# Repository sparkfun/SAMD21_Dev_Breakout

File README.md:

SparkFun SAMD21 Dev Breakout
========================================

[*SparkFun SAMD21 Dev Breakout (DEV-13672)*](https://www.sparkfun.com/products/13672)

The SAMD21 Dev Breakout is an Arduino-sized breakout for the Atmel [ATSAMD21G18](http://www.atmel.com/devices/ATSAMD21G18A.aspx), a 32-bit ARM Cortex-M0+ processor with 256KB flash, 32KB SRAM, and an operating speed of up to 48MHz. The SAMD21 is compatible with the Arduino IDE, and libraries for the Arduino Zero.

Repository Contents
-------------------

* **/Documentation** - Data sheets, additional product information
* **/Firmware** - SAM_BA SAMD21 Bootloader
* **/Hardware** - Eagle design files (.brd, .sch)
* **/Production** - Production panel files (.brd)

Documentation
--------------
* **[Hookup Guide](https://learn.sparkfun.com/tutorials/samd21-Devdev-breakout-hookup-guide/resources--going-further)** - Basic hookup guide for the SAMD21 Dev Breakout.

Product Versions
----------------
* [DEV-13672](https://www.sparkfun.com/products/13672) - Initial product release - v10.
* [DEV-13672](https://www.sparkfun.com/products/13664) - The SparkFun SAMD21 _Mini_ Breakout -- a similar, Arduino-shaped version of this board.

Version History
---------------
* [v1.0](https://github.com/sparkfun/SAMD21_Dev_Breakout/tree/v10) - Initial release 

License Information
-------------------

This product is _**open source**_! 

Please review the LICENSE.md file for license information. 

If you have any questions or concerns on licensing, please contact techsupport@sparkfun.com.

Distributed as-is; no warranty is given.

- Your friends at SparkFun.

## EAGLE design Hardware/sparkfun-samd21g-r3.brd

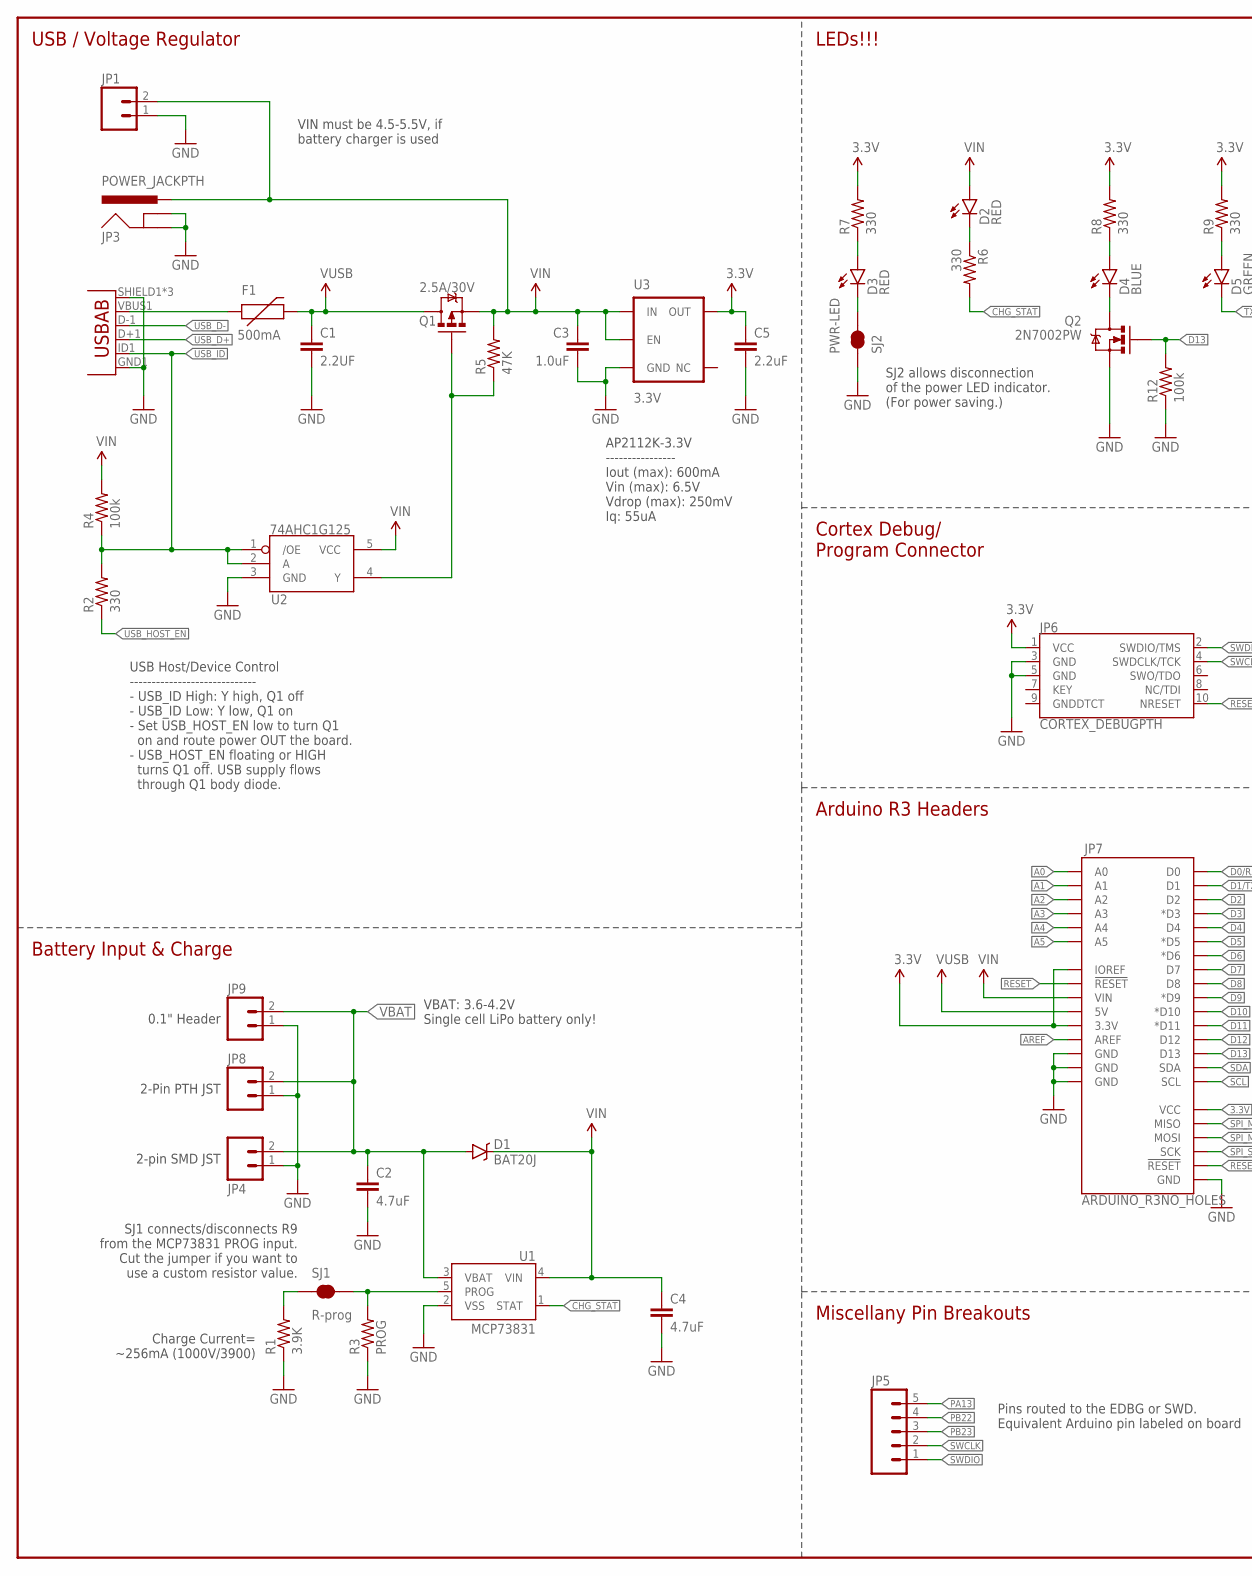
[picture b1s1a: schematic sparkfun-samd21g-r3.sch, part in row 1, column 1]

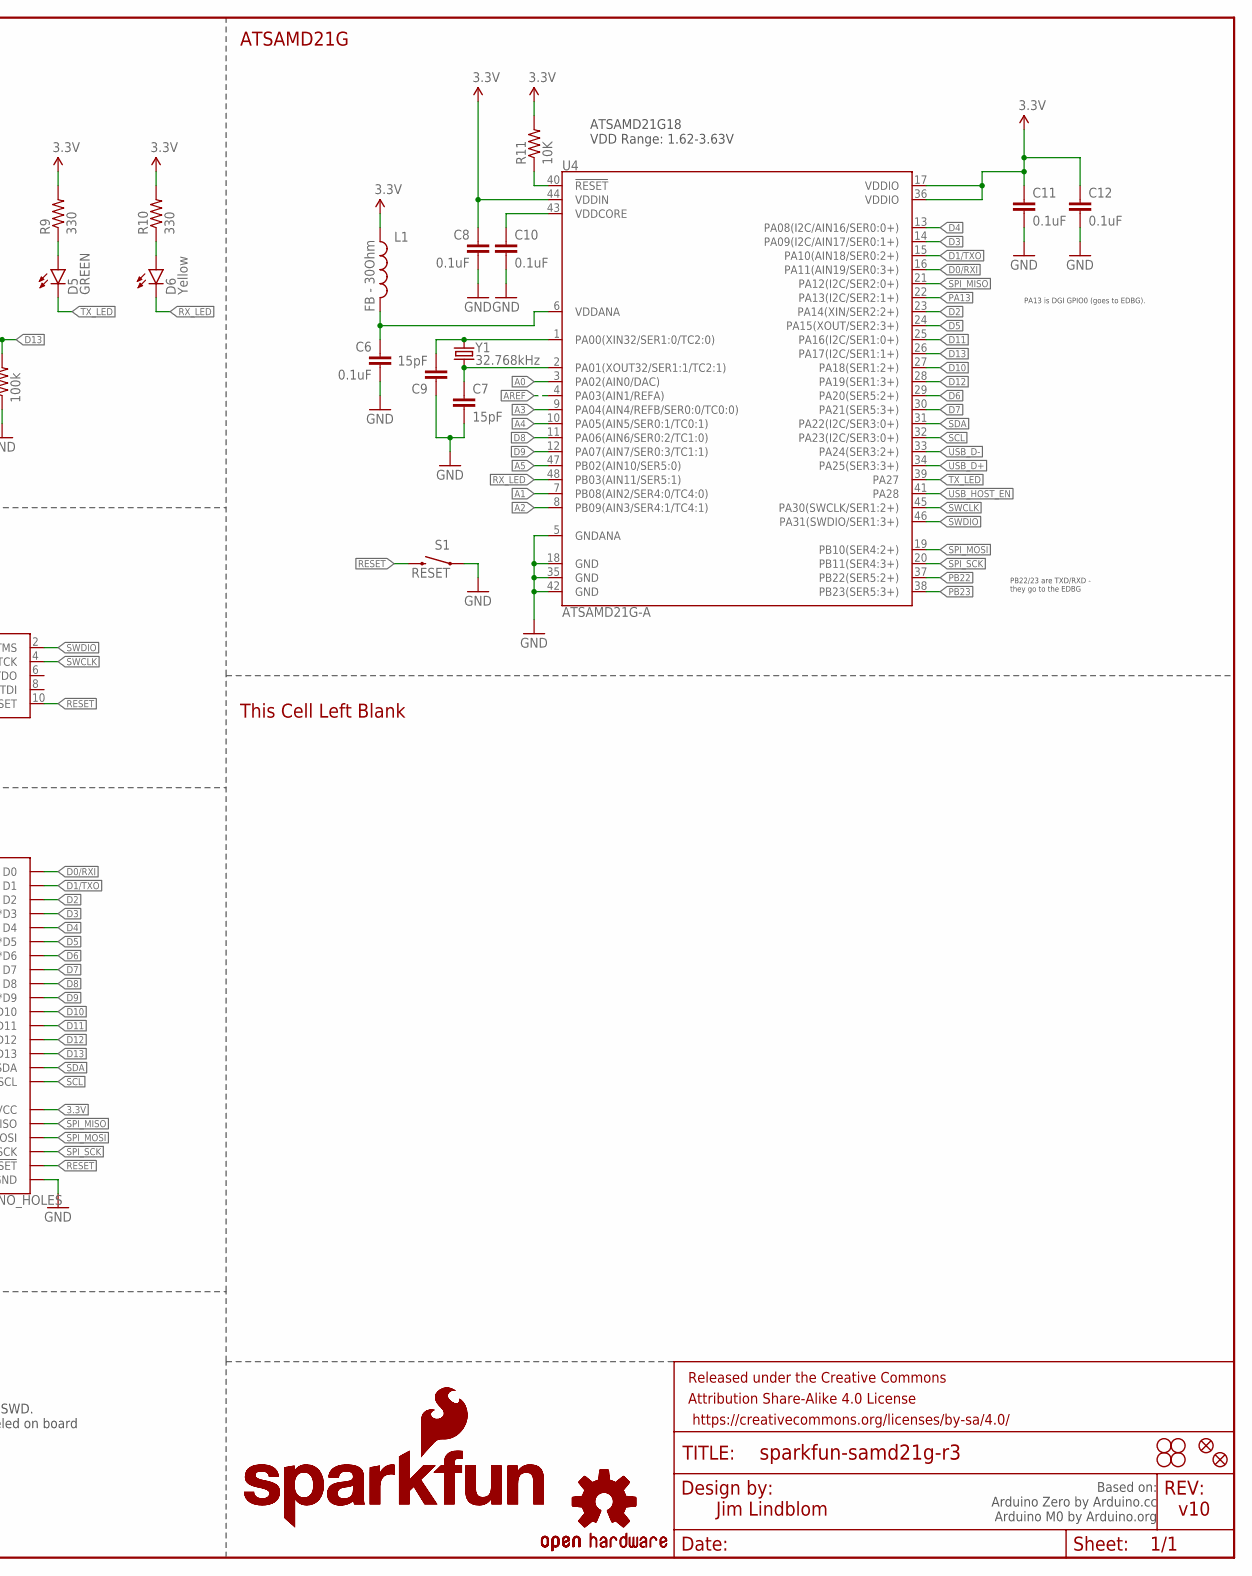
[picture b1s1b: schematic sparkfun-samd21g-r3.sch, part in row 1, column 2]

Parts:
C1: 2.2UF; 1206
C2, C4: 4.7uF; 0603-CAP
C3: 1.0uF; 0805-CAP
C5: 2.2uF; 0603-CAP
C6, C8, C10, C11, C12: 0.1uF; 0603-CAP
C7, C9: 15pF; 0603-CAP
D1: BAT20J; SOD-323
D2, D3: RED; LED-0603
D4: BLUE; LED-0603
D5: GREEN; LED-0603
D6: Yellow; LED-0603
F1: 500mA; PTC-1206
FID1, FID2: FIDUCIAL1X2; FIDUCIAL-1X2
FRAME1: FRAME-LEDGER; CREATIVE_COMMONS
JP1: M02PTH; 1X02
JP2: USB-ABCONN-11794; USB-AB-MICRO-SMD_V03
JP3: POWER_JACKPTH; POWER_JACK_PTH
JP4: M02-JST-2MM-SMT; JST-2-SMD
JP5: M05NO_SILK; 1X05_NO_SILK
JP6: CORTEX_DEBUGPTH; 2X5-PTH-1.27MM
JP7: ARDUINO_R3NO_HOLES; ARDUINO_R3_NO_HOLES
JP8: M02-JST-2-PTH-NO_SILK; JST-2-PTH-NS
JP9: M021X02_NO_SILK; 1X02_NO_SILK
L1: FB - 30Ohm; 0603
LOGO1: SFE_LOGO_NAME_FLAME.2_INCH; SFE_LOGO_NAME_FLAME_.2
LOGO2: SFE_LOGO_NAME_FLAME.4_INCH; SFE_LOGO_NAME_FLAME_.4
LOGO3: OSHW-LOGOS; OSHW-LOGO-S
LOGO4: OSHW-LOGOL; OSHW-LOGO-L
Q1: 2.5A/30V; SOT23-3
Q2: 2N7002PW; SOT323
R1: 3.9K; 0603
R2, R6, R7, R8, R9, R10: 330; 0603-RES
R3: PROG; 1/6W-RES
R4, R12: 100k; 0603-RES
R5: 47K; 0603-RES
R11: 10K; 0603-RES
S1: RESET; TACTILE-SWITCH-SMD
SJ1: R-prog; PAD-JUMPER-2-NC_BY_TRACE_YES_SILK
SJ2: PWR-LED; PAD-JUMPER-2-NC_BY_TRACE_NO_SILK
STANDOFF1, STANDOFF2, STANDOFF3, STANDOFF4: STAND-OFF
U1: MCP73831; SOT23-5
U2: 74AHC1G125; SOT23-5
U3: 3.3V; SOT23-5
U4: ATSAMD21G-A; TQFP-48
Y1: 32.768kHz; CRYSTAL-SMD-3.2X1.5MM

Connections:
3.3V: C5.1, C8.1, C11.1, C12.1, JP6.1 (VCC), JP7.3.3V, JP7.IOREF, JP7.VCC, L1.1, R7.2, R8.2, R9.2, R10.2, R11.2, U3.5 (OUT), U4.17 (VDDIO), U4.36 (VDDIO), U4.44 (VDDIN)
!RESET: JP6.10 (NRESET), JP7.RESET@1 (!RESET!), JP7.RESET@2 (!RESET!), R11.1, S1.3 (2), U4.40 (!RESET!)
A0: JP7.A0, U4.3 (PA02(AIN0/DAC))
A1: JP7.A1, U4.7 (PB08(AIN2/SER4:0/TC4:0))
A2: JP7.A2, U4.8 (PB09(AIN3/SER4:1/TC4:1))
A3: JP7.A3, U4.9 (PA04(AIN4/REFB/SER0:0/TC0:0))
A4: JP7.A4, U4.10 (PA05(AIN5/SER0:1/TC0:1))
A5: JP7.A5, U4.47 (PB02(AIN10/SER5:0))
AREF: JP7.AREF, U4.4 (PA03(AIN1/REFA))
CHG_STAT: R6.2, U1.1 (STAT)
D0/RXI: JP7.D0, U4.16 (PA11(AIN19/SER0:3+))
D1/TXO: JP7.D1, U4.15 (PA10(AIN18/SER0:2+))
D2: JP7.D2, U4.23 (PA14(XIN/SER2:2+))
D3: JP7.D3 (*D3), U4.14 (PA09(I2C/AIN17/SER0:1+))
D4: JP7.D4, U4.13 (PA08(I2C/AIN16/SER0:0+))
D5: JP7.D5 (*D5), U4.24 (PA15(XOUT/SER2:3+))
D6: JP7.D6 (*D6), U4.29 (PA20(SER5:2+))
D7: JP7.D7, U4.30 (PA21(SER5:3+))
D8: JP7.D8, U4.11 (PA06(AIN6/SER0:2/TC1:0))
D9: JP7.D9 (*D9), U4.12 (PA07(AIN7/SER0:3/TC1:1))
D10: JP7.D10 (*D10), U4.27 (PA18(SER1:2+))
D11: JP7.D11 (*D11), U4.25 (PA16(I2C/SER1:0+))
D12: JP7.D12, U4.28 (PA19(SER1:3+))
D13: JP7.D13, Q2.1 (G), R12.2, U4.26 (PA17(I2C/SER1:1+))
GND: C1.2, C2.2, C3.2, C4.2, C5.2, C6.2, C7.2, C8.2, C9.1, C10.2, C11.2, C12.2, JP1.1, JP2.GND1 (GND), JP2.SHIELD1 (SHIELD), JP2.SHIELD2 (SHIELD), JP2.SHIELD3 (SHIELD), JP3.GND, JP3.GNDBREAK, JP4.1 (2), JP6.3 (GND), JP6.5 (GND), JP7.GND@1 (GND), JP7.GND@2 (GND), JP7.GND@3 (GND), JP7.GND@4 (GND), JP8.1, JP9.1, Q2.2 (S), R1.1, R3.1, R12.1, S1.1, SJ2.1, U1.2 (VSS), U2.3 (GND), U3.2 (GND), U4.5 (GNDANA), U4.18 (GND), U4.35 (GND), U4.42 (GND)
unnamed: F1.1, JP2.VBUS1 (VBUS)
unnamed: C9.2, U4.1 (PA00(XIN32/SER1:0/TC2:0)), Y1.P$2 (2)
unnamed: D4.C, Q2.3 (D)
unnamed: C7.1, U4.2 (PA01(XOUT32/SER1:1/TC2:1)), Y1.P$1 (1)
unnamed: D3.A, R7.1
unnamed: D4.A, R8.1
unnamed: D2.C, R6.1
unnamed: D5.A, R9.1
unnamed: D6.A, R10.1
unnamed: D3.C, SJ2.2
unnamed: R1.2, SJ1.1
unnamed: R3.2, SJ1.2, U1.5 (PROG)
PA13: JP5.5, U4.22 (PA13(I2C/SER2:1+))
PB22: JP5.4, U4.37 (PB22(SER5:2+))
PB23: JP5.3, U4.38 (PB23(SER5:3+))
RX_LED: D6.C, U4.48 (PB03(AIN11/SER5:1))
SCL: JP7.SCL, U4.32 (PA23(I2C/SER3:0+))
SDA: JP7.SDA, U4.31 (PA22(I2C/SER3:0+))
SPI_MISO: JP7.MISO, U4.21 (PA12(I2C/SER2:0+))
SPI_MOSI: JP7.MOSI, U4.19 (PB10(SER4:2+))
SPI_SCK: JP7.SCK, U4.20 (PB11(SER4:3+))
SWCLK: JP5.2, JP6.4 (SWDCLK/TCK), U4.45 (PA30(SWCLK/SER1:2+))
SWDIO: JP5.1, JP6.2 (SWDIO/TMS), U4.46 (PA31(SWDIO/SER1:3+))
TX_LED: D5.C, U4.39 (PA27)
USB_D+: JP2.D+1 (D+), U4.34 (PA25(SER3:3+))
USB_D-: JP2.D-1 (D-), U4.33 (PA24(SER3:2+))
USB_HOST_EN: R2.1, U4.41 (PA28)
USB_HOST_POWER_EN: Q1.1 (G), R5.1, U2.4 (Y)
USB_ID: JP2.ID1 (USBID), R2.2, R4.1, U2.1 (/OE), U2.2 (A)
VBAT: C2.1, D1.A, JP4.2 (1), JP8.2, JP9.2, U1.3 (VBAT)
VDDANA: C6.1, L1.2, U4.6 (VDDANA)
VDDCORE: C10.1, U4.43 (VDDCORE)
VIN: C3.1, C4.1, D1.C, D2.A, JP1.2, JP3.PWR, JP7.VIN, Q1.2 (S), R4.2, R5.2, U1.4 (VIN), U2.5 (VCC), U3.1 (IN), U3.3 (EN)
VUSB: C1.1, F1.2, JP7.5V, Q1.3 (D)

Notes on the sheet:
PB22/23 are TXD/RXD - they go to the EDBG
PA13 is DGI GPIO0 (goes to EDBG).
USB / Voltage Regulator
LEDs!!!
Cortex Debug/ Program Connector
Arduino R3 Headers
ATSAMD21G
Jim Lindblom
v10
Charge Current= ~256mA (1000V/3900)
SJ1 connects/disconnects R9 from the MCP73831 PROG input. Cut the jumper if you want to use a custom resistor value.
Battery Input & Charge
SJ2 allows disconnection of the power LED indicator. (For power saving.)
Miscellany Pin Breakouts
This Cell Left Blank
VIN must be 4.5-5.5V, if battery charger is used
ATSAMD21G18 VDD Range: 1.62-3.63V
Based on: Arduino Zero by Arduino.cc Arduino M0 by Arduino.org
0.1" Header
2-Pin PTH JST
2-pin SMD JST
AP2112K-3.3V ---------------- Iout (max): 600mA Vin (max): 6.5V Vdrop (max): 250mV Iq: 55uA
USB Host/Device Control ----------------------------- - USB_ID High: Y high, Q1 off - USB_ID Low: Y low, Q1 on - Set USB_HOST_EN low to turn Q1 on and route power OUT the board. - USB_HOST_EN floating or HIGH turns Q1 off. USB supply flows through Q1 body diode.
Pins routed to the EDBG or SWD. Equivalent Arduino pin labeled on board
VBAT: 3.6-4.2V Single cell LiPo battery only\!

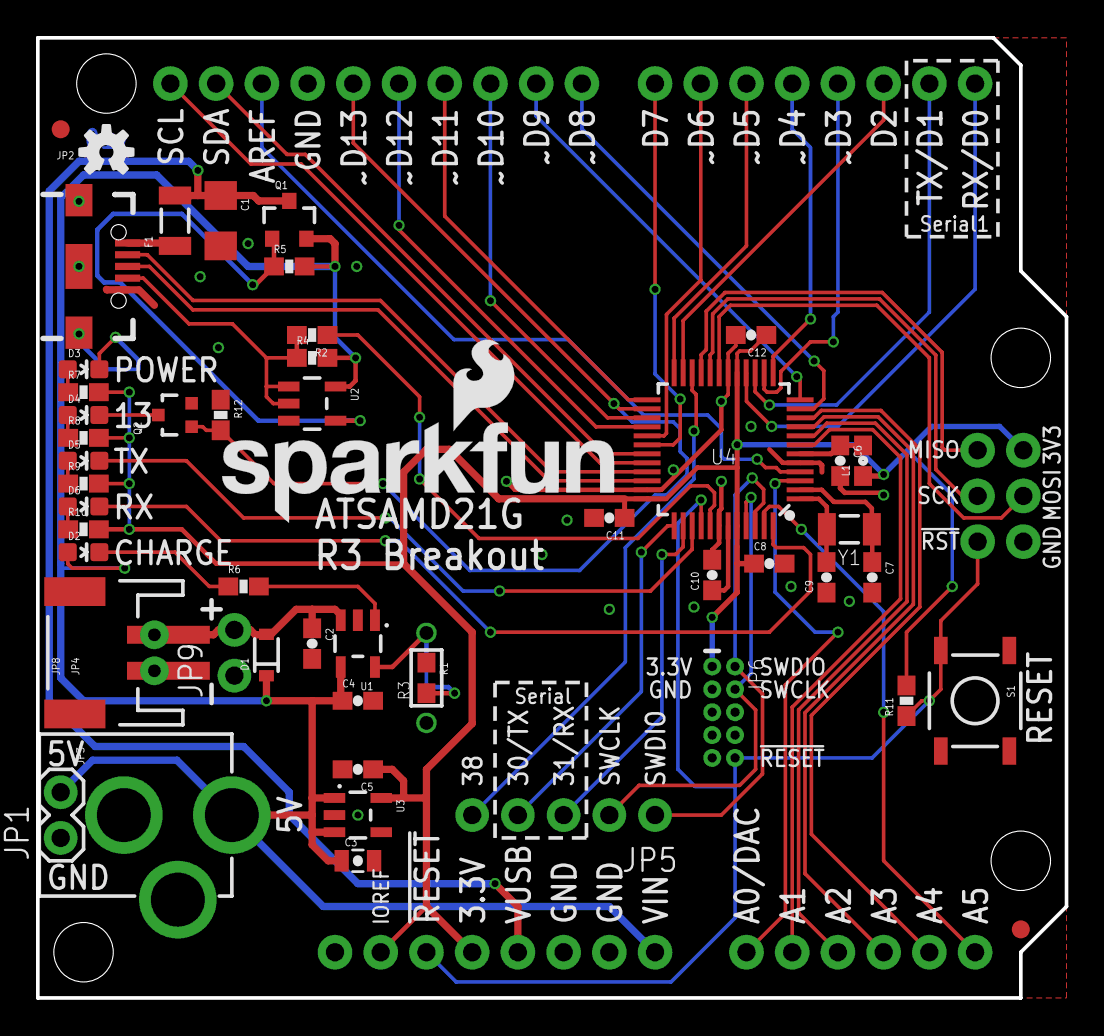
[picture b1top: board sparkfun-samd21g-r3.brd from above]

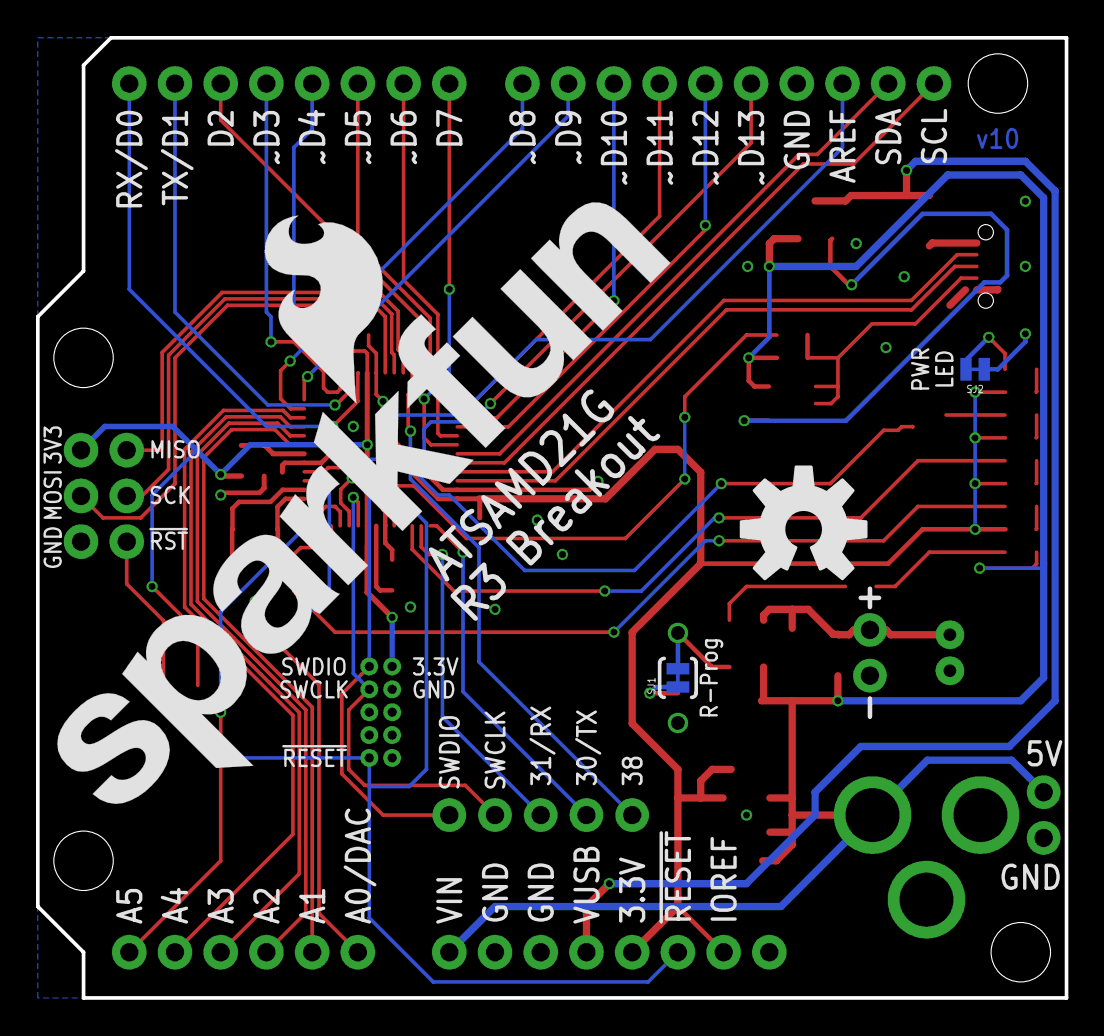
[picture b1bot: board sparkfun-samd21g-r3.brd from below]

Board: 2 copper layers, 57.1 x 53.3 mm, 62 parts (4 on the bottom side), 59 nets.

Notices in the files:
parts and their libraries:
SparkFun-Capacitors: Licensing: Creative Commons ShareAlike 4.0 International - https://creativecommons.org/licenses/by-sa/4.0
SparkFun-Aesthetics: Released under the Creative Commons Attribution Share-Alike 4.0 License
SparkFun-Aesthetics: https://creativecommons.org/licenses/by-sa/4.0
